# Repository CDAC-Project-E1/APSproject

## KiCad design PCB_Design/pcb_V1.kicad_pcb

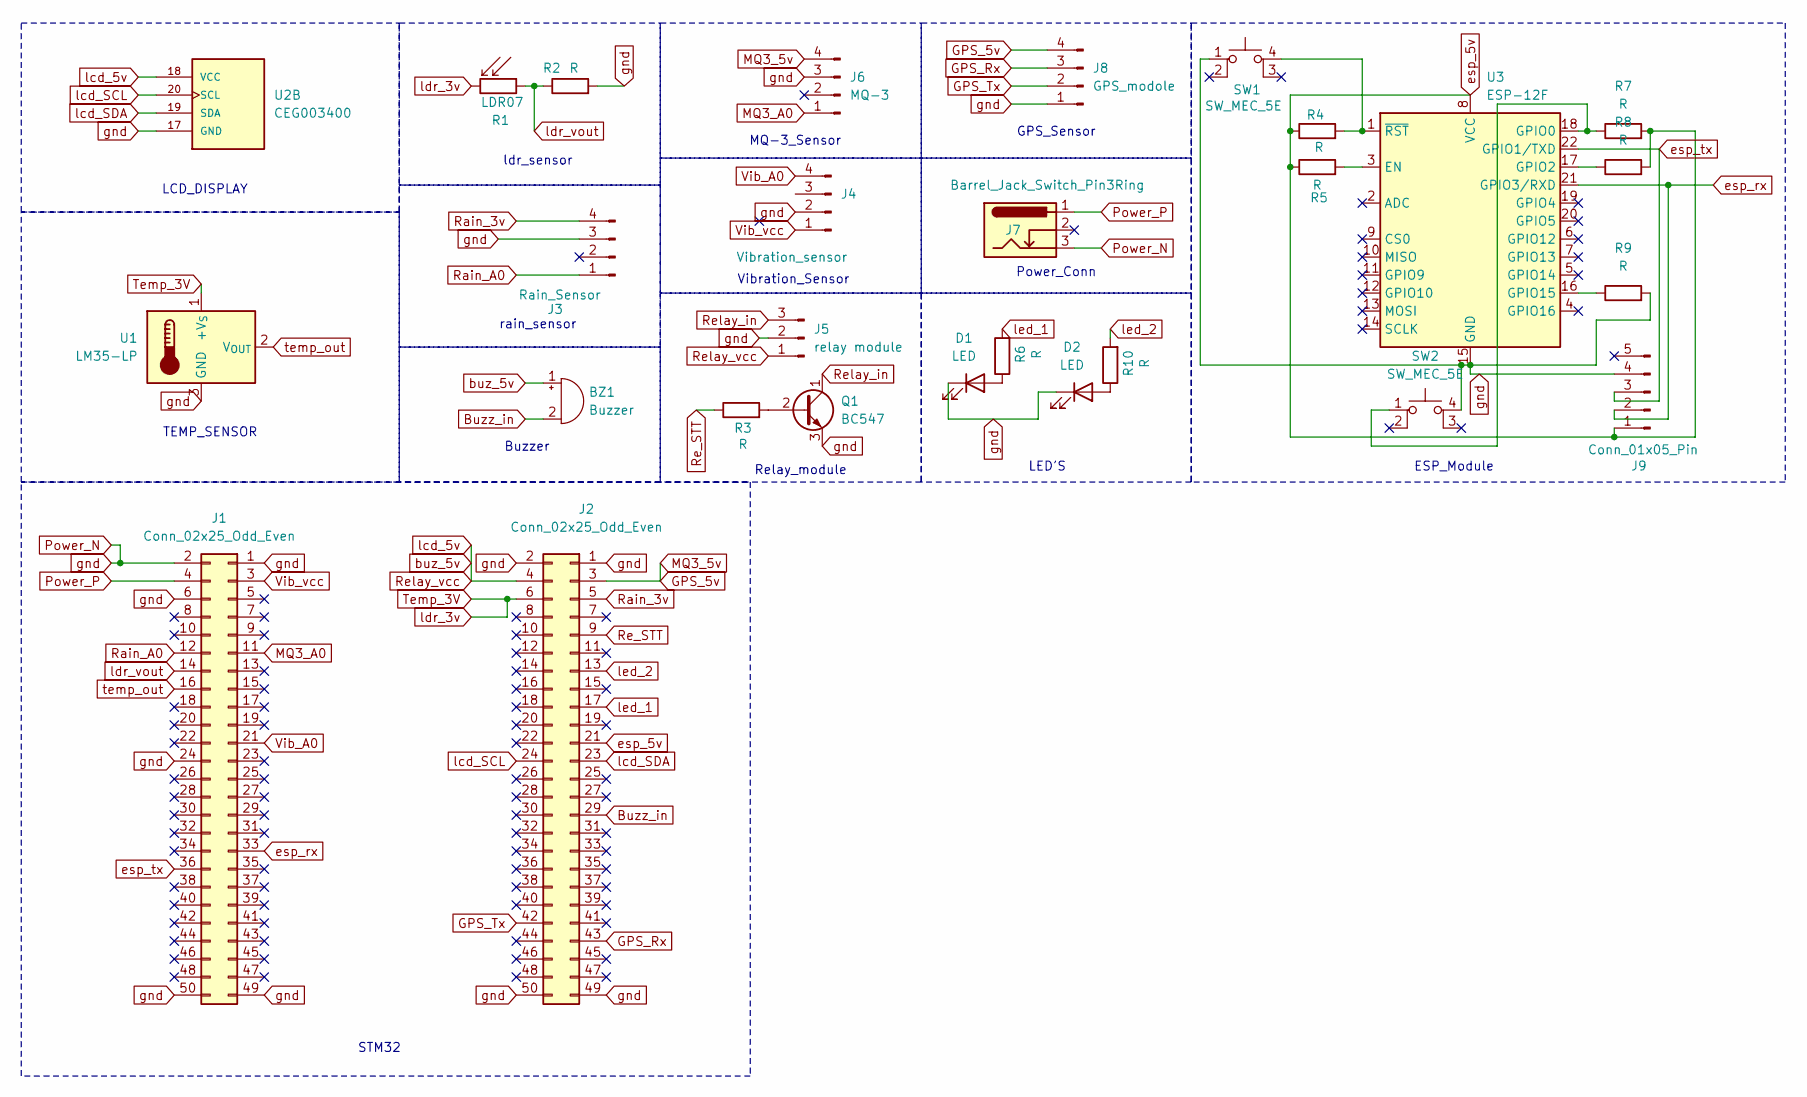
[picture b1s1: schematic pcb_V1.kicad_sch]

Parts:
BZ1: Buzzer; Buzzer_15x7.5RM7.6
D1, D2: LED; LED_D5.0mm_Clear
J1, J2: Conn_02x25_Odd_Even; PinSocket_2x25_P2.54mm_Vertical
J3: Rain_Sensor; PinHeader_1x04_P2.54mm_Vertical
J4: Vibration_sensor; PinHeader_1x04_P2.54mm_Vertical
J5: relay module; PinHeader_1x03_P2.54mm_Vertical
J6: MQ-3; PinHeader_1x04_P2.54mm_Vertical
J7: Barrel_Jack_Switch_Pin3Ring; BarrelJack_Horizontal
J8: GPS_modole; PinHeader_1x04_P2.54mm_Vertical
J9: Conn_01x05_Pin; PinHeader_1x05_P2.54mm_Vertical
Q1: BC547; TO-92_Inline
R1: LDR07; R_LDR_5.1x4.3mm_P3.4mm_Vertical
R2, R3, R4, R5, R6, R7, R8, R9, R10: R; R_Axial_DIN0207_L6.3mm_D2.5mm_P10.16mm_Horizontal
SW1, SW2: SW_MEC_5E; SW_Push_2P1T_Toggle_CK_PVA1xxH4xxxxxxV2
U1: LM35-LP; TO-92_Inline
U2: CEG003400; MODULE_CEG003400; PARTREV N/A
U3: ESP-12F; ESP-12E

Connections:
Buzz_in: BZ1.2 (-), J2.29
GPS_5v: J2.3, J6.4, J8.4
GPS_Rx: J2.43, J8.3
GPS_Tx: J2.42, J8.2
MQ3_A0: J1.11, J6.1
unnamed: D1.2 (A), R6.1
unnamed: D2.2 (A), R10.1
unnamed: Q1.2 (B), R3.2
unnamed: R4.2, SW1.4 (A), U3.1 (~RST)
unnamed: R5.2, U3.3 (EN)
unnamed: R7.1, SW2.1, U3.18 (GPIO0)
unnamed: R8.1, U3.17 (GPIO2)
unnamed: R9.1, U3.16 (GPIO15)
Power_N: D1.1 (K), D2.1 (K), J1.1, J1.2, J1.6, J1.24, J1.49, J1.50, J2.1, J2.2, J2.49, J2.50, J3.3, J4.2, J5.2, J6.3, J7.3, J8.1, J9.4, Q1.3 (E), R2.2, R9.2, SW1.1, SW2.4 (A), U1.3 (GND), U2.17 (GND), U3.15 (GND)
Power_P: J1.4, J7.1
Rain_3v: J2.5, J3.4
Rain_A0: J1.12, J3.1
Re_STT: J2.9, R3.1
Relay_in: J5.3, Q1.1 (C)
Relay_vcc: BZ1.1 (+), J2.4, J5.1, U2.18 (VCC)
Temp_3V: J2.6, R1.2, U1.1 (+V_{S})
Vib_A0: J1.21, J4.4
Vib_vcc: J1.3, J4.1
esp_5v: J2.21, J9.1, R4.1, R5.1, R7.2, R8.2, U3.8 (VCC)
esp_rx: J1.33, J9.2, U3.21 (GPIO3/RXD)
esp_tx: J1.36, J9.3, U3.22 (GPIO1/TXD)
lcd_SCL: J2.24, U2.20 (SCL)
lcd_SDA: J2.23, U2.19 (SDA)
ldr_vout: J1.14, R1.1, R2.1
led_1: J2.17, R6.2
led_2: J2.13, R10.2
temp_out: J1.16, U1.2 (V_{OUT})

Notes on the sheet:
STM32
Relay_module
Power_Conn
LCD_DISPLAY
GPS_Sensor
rain_sensor
MQ-3_Sensor
Buzzer
ldr_sensor
LED'S
ESP_Module
Vibration_Sensor
TEMP_SENSOR

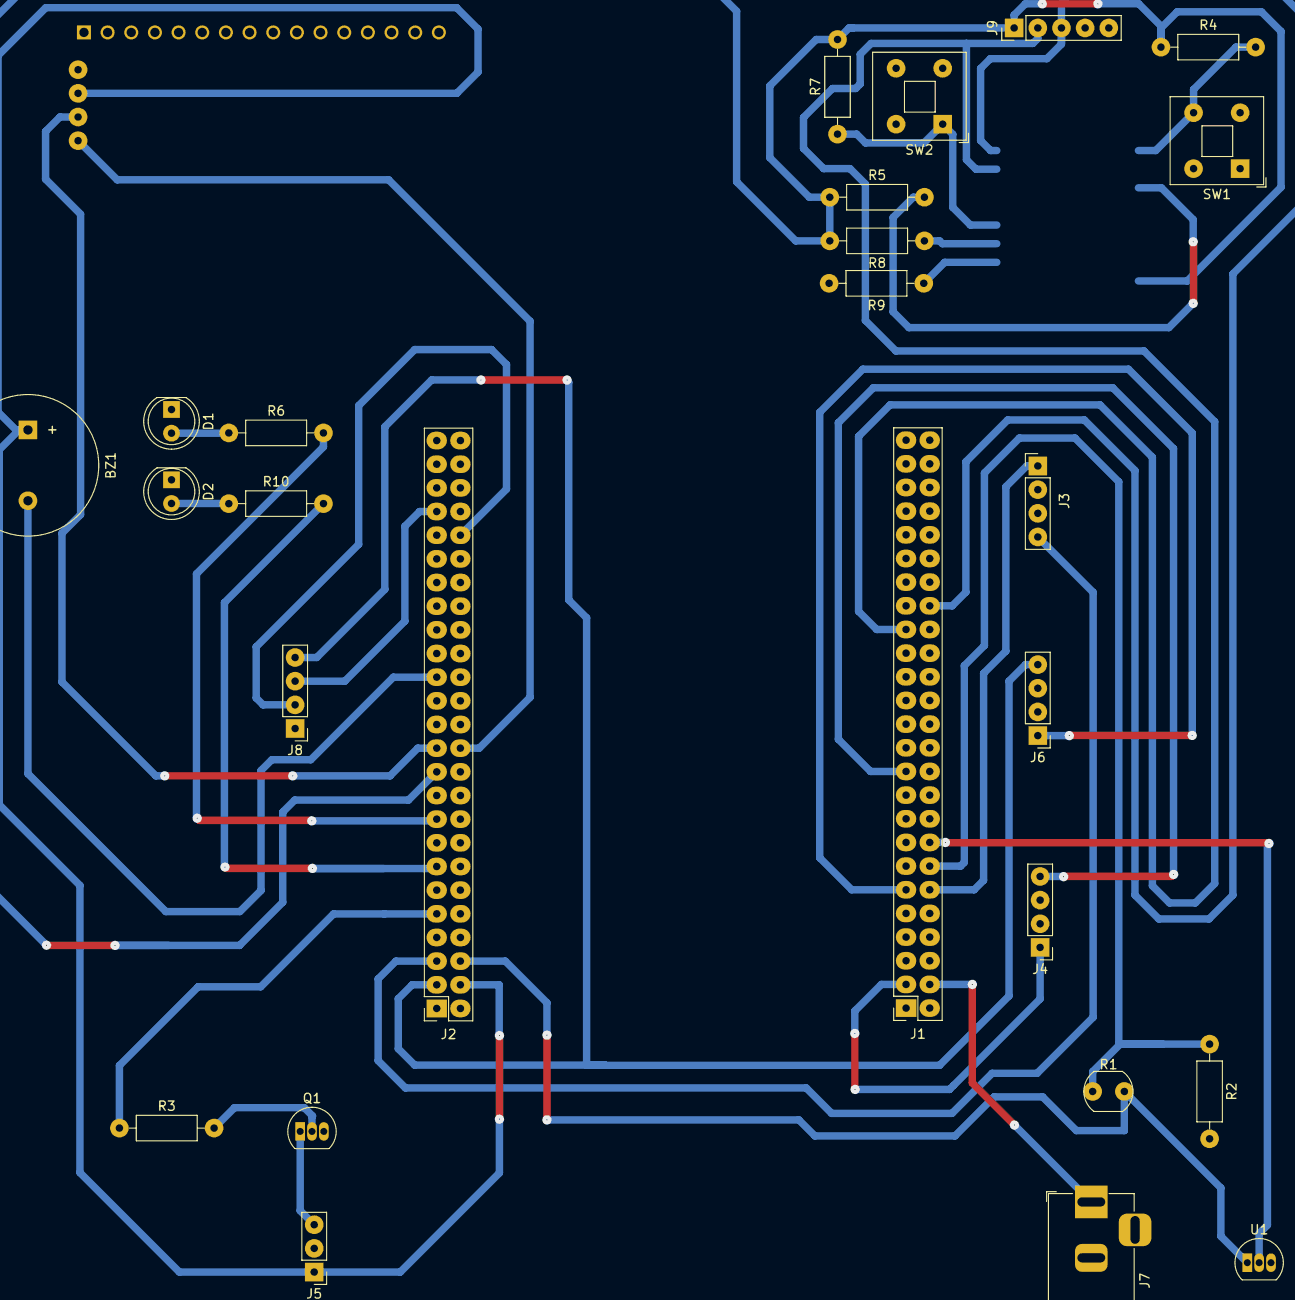
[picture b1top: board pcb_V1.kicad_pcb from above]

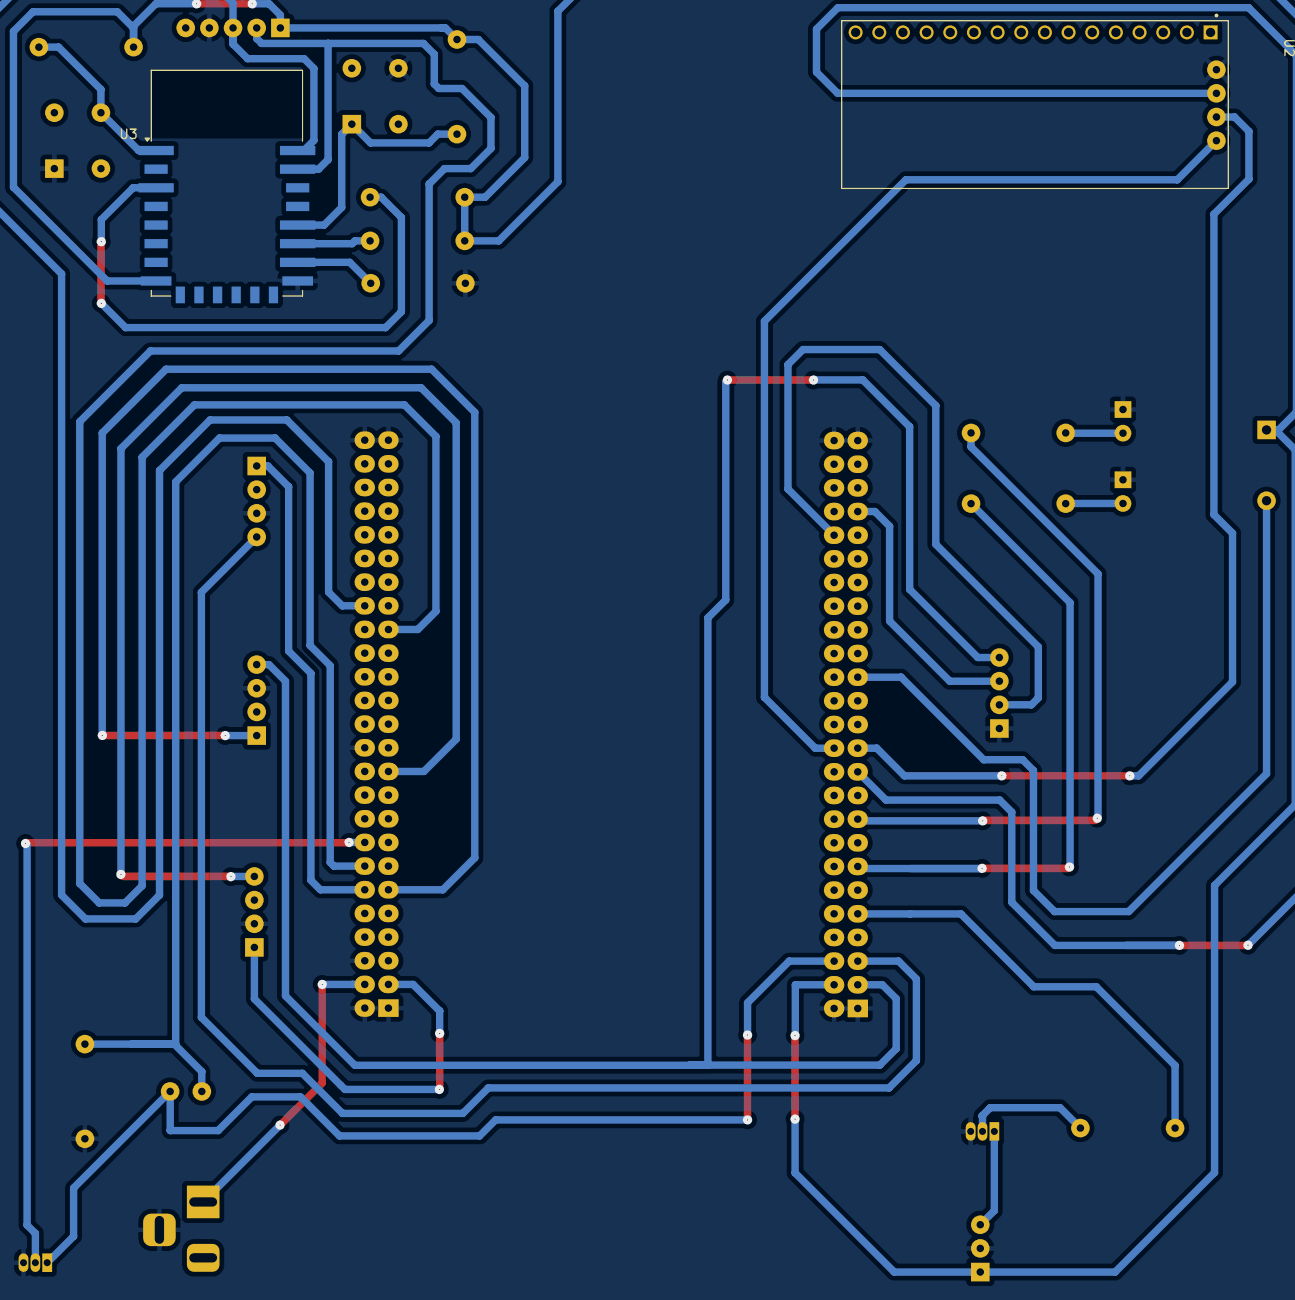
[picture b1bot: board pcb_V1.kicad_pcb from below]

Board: 2 copper layers, 28 parts (2 on the bottom side), 32 nets.

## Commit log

2025-07-02 Esp32_Datasheet
2025-07-03 Add files via upload
    LCD DOC's
2025-07-03 Add files via upload
    Sensor Datasheets
2025-07-05 HAL_LCD_code
2025-07-13 HAL_Rain_Sensor
2025-07-22 HAL_GPS_Code
2025-07-24 LM35_Datasheet
2025-07-24 HAL_LML_LM35 code
2025-07-24 Vibration sensor data
2025-07-24 Vibration Sensor info
2025-07-24 Study data lm35
2025-07-30 MQ3 Sensor
2025-07-30 LDR Sensor
2025-08-01 SMTP
2025-08-01 Socket_programing
2025-08-03 Rain_Seansor_Datasheet
2025-08-04 GSP_Neo6M_Datasheet
2025-08-05 Relay_Module_Datasheet
2025-08-05 HAL_Relay_LED_Buzzer
2025-08-07 PCB_Schematic_&_Circuit
2025-08-09 User manual
2025-08-09 Final_Complete_Code
2025-08-10 Block Diagram
